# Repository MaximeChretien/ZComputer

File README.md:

# ZComputer

This projects aims to build a computer based on a Z80 CPU from scratch.

## Introduction

The computer is designed as a set of boards, each having a specific function.

The current planned boards are:
- Main (CPU, RAM, ROM, ...)
- Basic I/O
- Interrupt (Interrupt vector decoding and prioritizing)
- UART
- Counter/Timer
- ADC and DAC
- Storage

Those boards will then connect on the base board through a unified connector.  
The base board also includes the power input and the reset button as well as a power LED.

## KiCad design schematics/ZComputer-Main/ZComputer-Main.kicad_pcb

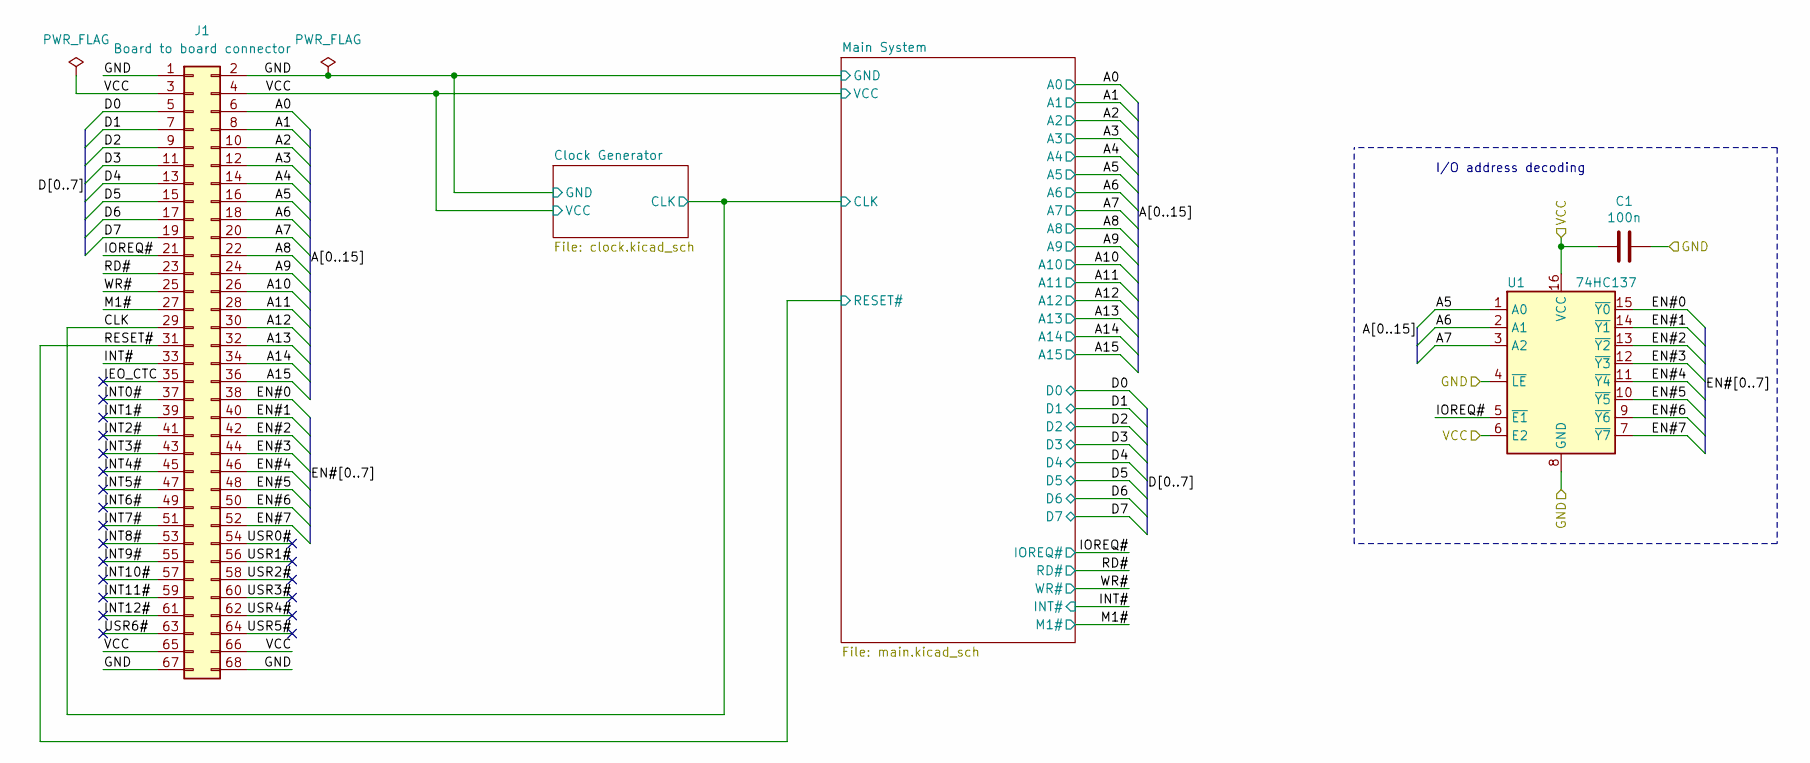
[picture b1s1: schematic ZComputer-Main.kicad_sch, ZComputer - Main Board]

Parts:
C1: 100n; C_Disc_D4.3mm_W1.9mm_P5.00mm
J1: Board to board connector; PinSocket_2x34_P2.54mm_Horizontal
U1: 74HC137; DIP-16_W7.62mm_Socket_LongPads

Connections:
/A0: J1.6; also elsewhere on the board
/A1: J1.8; also elsewhere on the board
/A2: J1.10; also elsewhere on the board
/A3: J1.12; also elsewhere on the board
/A4: J1.14; also elsewhere on the board
/A5: J1.16, U1.1 (A0); also elsewhere on the board
/A6: J1.18, U1.2 (A1); also elsewhere on the board
/A7: J1.20, U1.3 (A2); also elsewhere on the board
/A8: J1.22; also elsewhere on the board
/A9: J1.24; also elsewhere on the board
/A10: J1.26; also elsewhere on the board
/A11: J1.28; also elsewhere on the board
/A12: J1.30; also elsewhere on the board
/A13: J1.32; also elsewhere on the board
/A14: J1.34; also elsewhere on the board
/A15: J1.36; also elsewhere on the board
/CLK: J1.29; also elsewhere on the board
/D0: J1.5; also elsewhere on the board
/D1: J1.7; also elsewhere on the board
/D2: J1.9; also elsewhere on the board
/D3: J1.11; also elsewhere on the board
/D4: J1.13; also elsewhere on the board
/D5: J1.15; also elsewhere on the board
/D6: J1.17; also elsewhere on the board
/D7: J1.19; also elsewhere on the board
/EN#0: J1.38, U1.15 (~Y0)
/EN#1: J1.40, U1.14 (~Y1)
/EN#2: J1.42, U1.13 (~Y2)
/EN#3: J1.44, U1.12 (~Y3)
/EN#4: J1.46, U1.11 (~Y4)
/EN#5: J1.48, U1.10 (~Y5)
/EN#6: J1.50, U1.9 (~Y6)
/EN#7: J1.52, U1.7 (~Y7)
/GND: C1.1, J1.1, J1.2, J1.67, J1.68, U1.4 (~LE), U1.8 (GND); also elsewhere on the board
/IEO_CTC: J1.35
/INT0#: J1.37
/INT1#: J1.39
/INT2#: J1.41
/INT3#: J1.43
/INT4#: J1.45
/INT5#: J1.47
/INT6#: J1.49
/INT7#: J1.51
/INT8#: J1.53
/INT9#: J1.55
/INT10#: J1.57
/INT11#: J1.59
/INT12#: J1.61
/INT#: J1.33; also elsewhere on the board
/IOREQ#: J1.21, U1.5 (~E1); also elsewhere on the board
/M1#: J1.27; also elsewhere on the board
/RD#: J1.23; also elsewhere on the board
/RESET#: J1.31; also elsewhere on the board
/USR0#: J1.54
/USR1#: J1.56
/USR2#: J1.58
/USR3#: J1.60
/USR4#: J1.62
/USR5#: J1.64
/USR6#: J1.63
/VCC: C1.2, J1.3, J1.4, J1.65, J1.66, U1.6 (E2), U1.16 (VCC); also elsewhere on the board
/WR#: J1.25; also elsewhere on the board

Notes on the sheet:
I/O address decoding

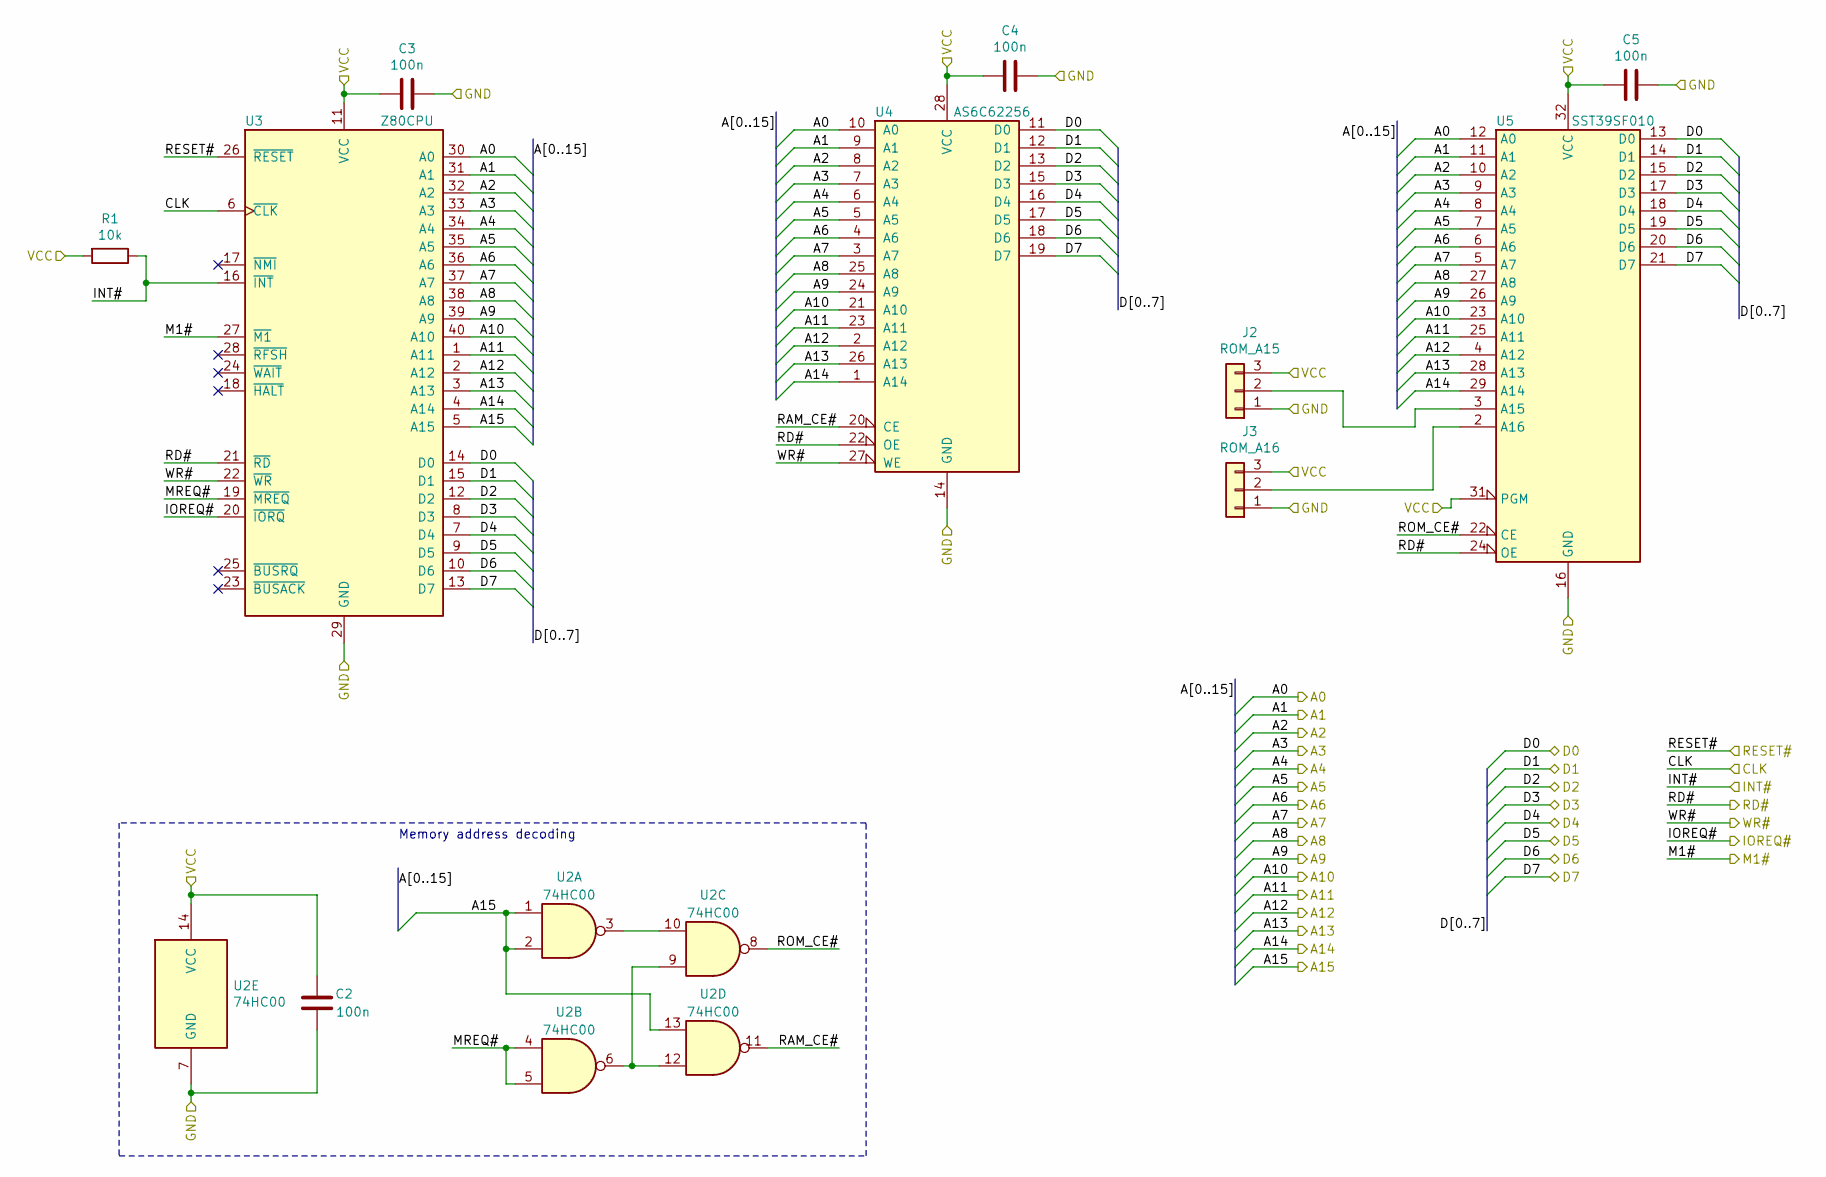
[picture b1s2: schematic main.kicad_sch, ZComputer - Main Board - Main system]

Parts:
C2, C3, C4, C5: 100n; C_Disc_D4.3mm_W1.9mm_P5.00mm
J2: ROM_A15; PinHeader_1x03_P2.54mm_Vertical
J3: ROM_A16; PinHeader_1x03_P2.54mm_Vertical
R1: 10k; R_Axial_DIN0207_L6.3mm_D2.5mm_P10.16mm_Horizontal
U2: 74HC00; DIP-14_W7.62mm_Socket_LongPads
U3: Z80CPU; DIP-40_W15.24mm_Socket_LongPads
U4: AS6C62256; DIP-28_W15.24mm_Socket_LongPads
U5: SST39SF010; DIP-32_W15.24mm_Socket_LongPads

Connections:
/A0: U3.30 (A0), U4.10 (A0), U5.12 (A0); also elsewhere on the board
/A1: U3.31 (A1), U4.9 (A1), U5.11 (A1); also elsewhere on the board
/A2: U3.32 (A2), U4.8 (A2), U5.10 (A2); also elsewhere on the board
/A3: U3.33 (A3), U4.7 (A3), U5.9 (A3); also elsewhere on the board
/A4: U3.34 (A4), U4.6 (A4), U5.8 (A4); also elsewhere on the board
/A5: U3.35 (A5), U4.5 (A5), U5.7 (A5); also elsewhere on the board
/A6: U3.36 (A6), U4.4 (A6), U5.6 (A6); also elsewhere on the board
/A7: U3.37 (A7), U4.3 (A7), U5.5 (A7); also elsewhere on the board
/A8: U3.38 (A8), U4.25 (A8), U5.27 (A8); also elsewhere on the board
/A9: U3.39 (A9), U4.24 (A9), U5.26 (A9); also elsewhere on the board
/A10: U3.40 (A10), U4.21 (A10), U5.23 (A10); also elsewhere on the board
/A11: U3.1 (A11), U4.23 (A11), U5.25 (A11); also elsewhere on the board
/A12: U3.2 (A12), U4.2 (A12), U5.4 (A12); also elsewhere on the board
/A13: U3.3 (A13), U4.26 (A13), U5.28 (A13); also elsewhere on the board
/A14: U3.4 (A14), U4.1 (A14), U5.29 (A14); also elsewhere on the board
/A15: U2.1, U2.2, U2.13, U3.5 (A15); also elsewhere on the board
/CLK: U3.6 (~CLK); also elsewhere on the board
/D0: U3.14 (D0), U4.11 (D0), U5.13 (D0); also elsewhere on the board
/D1: U3.15 (D1), U4.12 (D1), U5.14 (D1); also elsewhere on the board
/D2: U3.12 (D2), U4.13 (D2), U5.15 (D2); also elsewhere on the board
/D3: U3.8 (D3), U4.15 (D3), U5.17 (D3); also elsewhere on the board
/D4: U3.7 (D4), U4.16 (D4), U5.18 (D4); also elsewhere on the board
/D5: U3.9 (D5), U4.17 (D5), U5.19 (D5); also elsewhere on the board
/D6: U3.10 (D6), U4.18 (D6), U5.20 (D6); also elsewhere on the board
/D7: U3.13 (D7), U4.19 (D7), U5.21 (D7); also elsewhere on the board
/GND: C2.1, C3.1, C4.1, C5.1, J2.1, J3.1, U2.7 (GND), U3.29 (GND), U4.14 (GND), U5.16 (GND); also elsewhere on the board
/INT#: R1.1, U3.16 (~INT); also elsewhere on the board
/IOREQ#: U3.20 (~IORQ); also elsewhere on the board
/M1#: U3.27 (~M1); also elsewhere on the board
/Main System/MREQ#: U2.4, U2.5, U3.19 (~MREQ)
/Main System/RAM_CE#: U2.11, U4.20 (CE)
/Main System/ROM_CE#: U2.8, U5.22 (CE)
/RD#: U3.21 (~RD), U4.22 (OE), U5.24 (OE); also elsewhere on the board
/RESET#: U3.26 (~RESET); also elsewhere on the board
/VCC: C2.2, C3.2, C4.2, C5.2, J2.3, J3.3, R1.2, U2.14 (VCC), U3.11 (VCC), U4.28 (VCC), U5.31 (PGM), U5.32 (VCC); also elsewhere on the board
/WR#: U3.22 (~WR), U4.27 (WE); also elsewhere on the board
unnamed: J2.2, U5.3 (A15)
unnamed: J3.2, U5.2 (A16)
unnamed: U2.3, U2.10
unnamed: U2.6, U2.9, U2.12

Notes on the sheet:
Memory address decoding

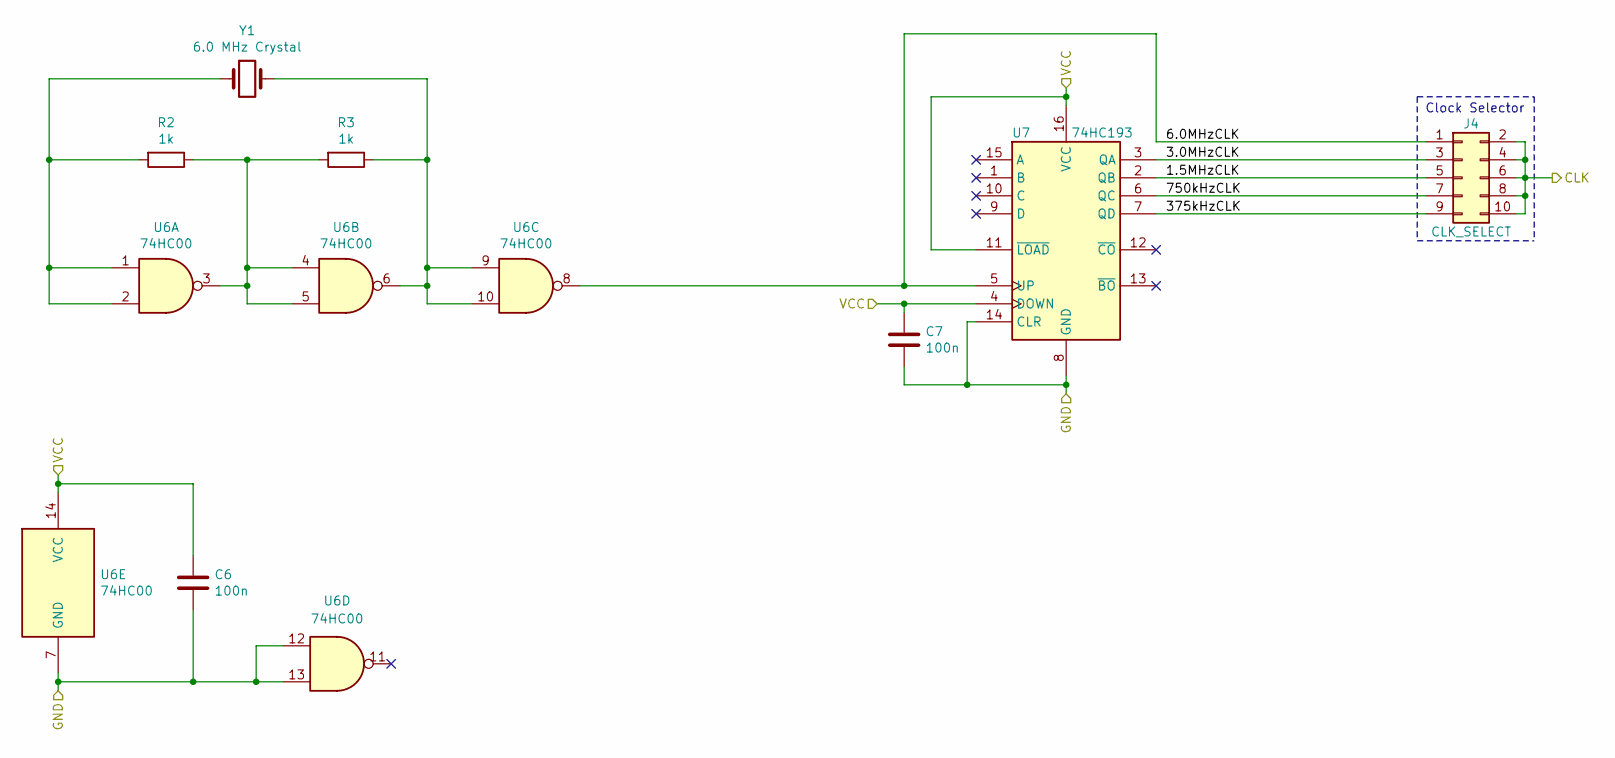
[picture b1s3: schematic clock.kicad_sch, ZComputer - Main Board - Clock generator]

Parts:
C6, C7: 100n; C_Disc_D4.3mm_W1.9mm_P5.00mm
J4: CLK_SELECT; PinHeader_2x05_P2.54mm_Vertical
R2, R3: 1k; R_Axial_DIN0207_L6.3mm_D2.5mm_P10.16mm_Horizontal
U6: 74HC00; DIP-14_W7.62mm_Socket_LongPads
U7: 74HC193; DIP-16_W7.62mm_Socket_LongPads
Y1: 6.0 MHz Crystal; Crystal_HC49-4H_Vertical

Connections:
/CLK: J4.2, J4.4, J4.6, J4.8, J4.10; also elsewhere on the board
/Clock Generator/1.5MHzCLK: J4.5, U7.2 (QB)
/Clock Generator/3.0MHzCLK: J4.3, U7.3 (QA)
/Clock Generator/6.0MHzCLK: J4.1, U6.8, U7.5 (UP)
/Clock Generator/375kHzCLK: J4.9, U7.7 (QD)
/Clock Generator/750kHzCLK: J4.7, U7.6 (QC)
/GND: C6.2, C7.2, U6.7 (GND), U6.12, U6.13, U7.8 (GND), U7.14 (CLR); also elsewhere on the board
/VCC: C6.1, C7.1, U6.14 (VCC), U7.4 (DOWN), U7.11 (~LOAD), U7.16 (VCC); also elsewhere on the board
unnamed: R2.1, R3.2, U6.3, U6.4, U6.5
unnamed: R2.2, U6.1, U6.2, Y1.1
unnamed: R3.1, U6.6, U6.9, U6.10, Y1.2

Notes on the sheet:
Clock Selector

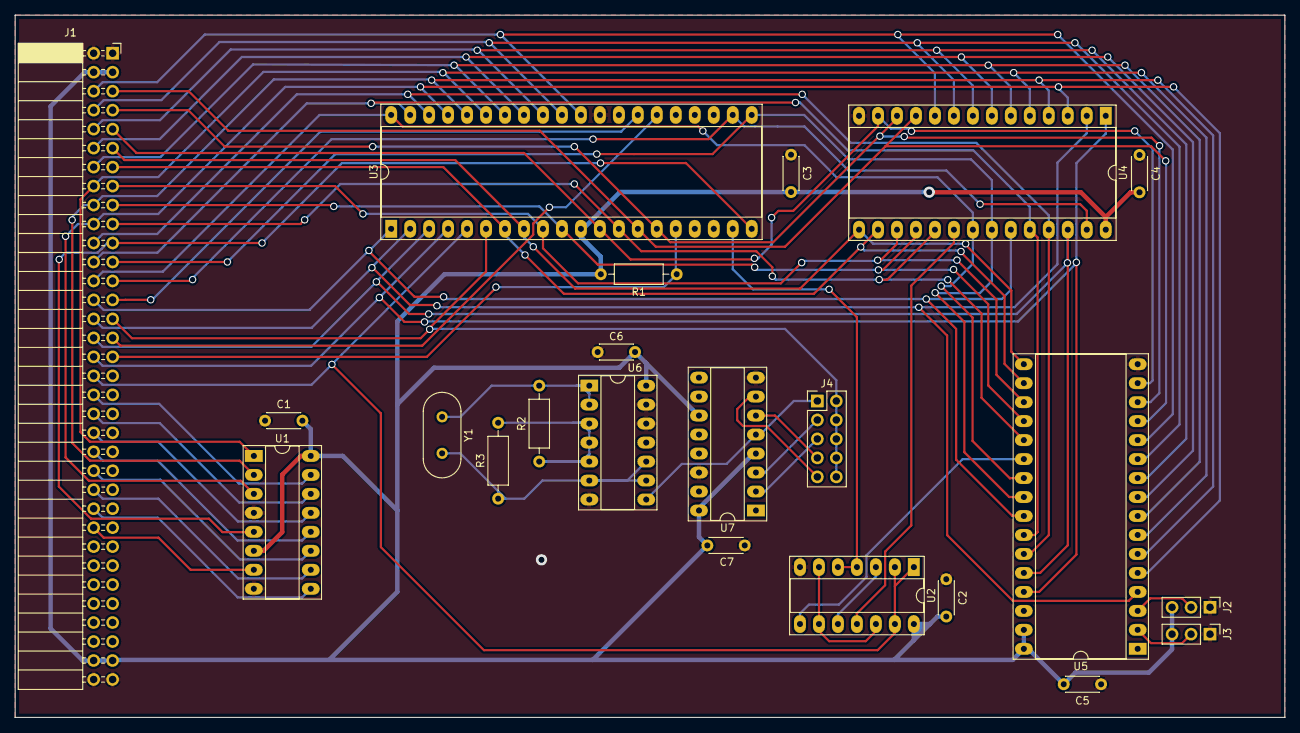
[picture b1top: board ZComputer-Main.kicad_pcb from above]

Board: 2 copper layers, 169.9 x 94.0 mm, 22 parts (0 on the bottom side), 56 nets.

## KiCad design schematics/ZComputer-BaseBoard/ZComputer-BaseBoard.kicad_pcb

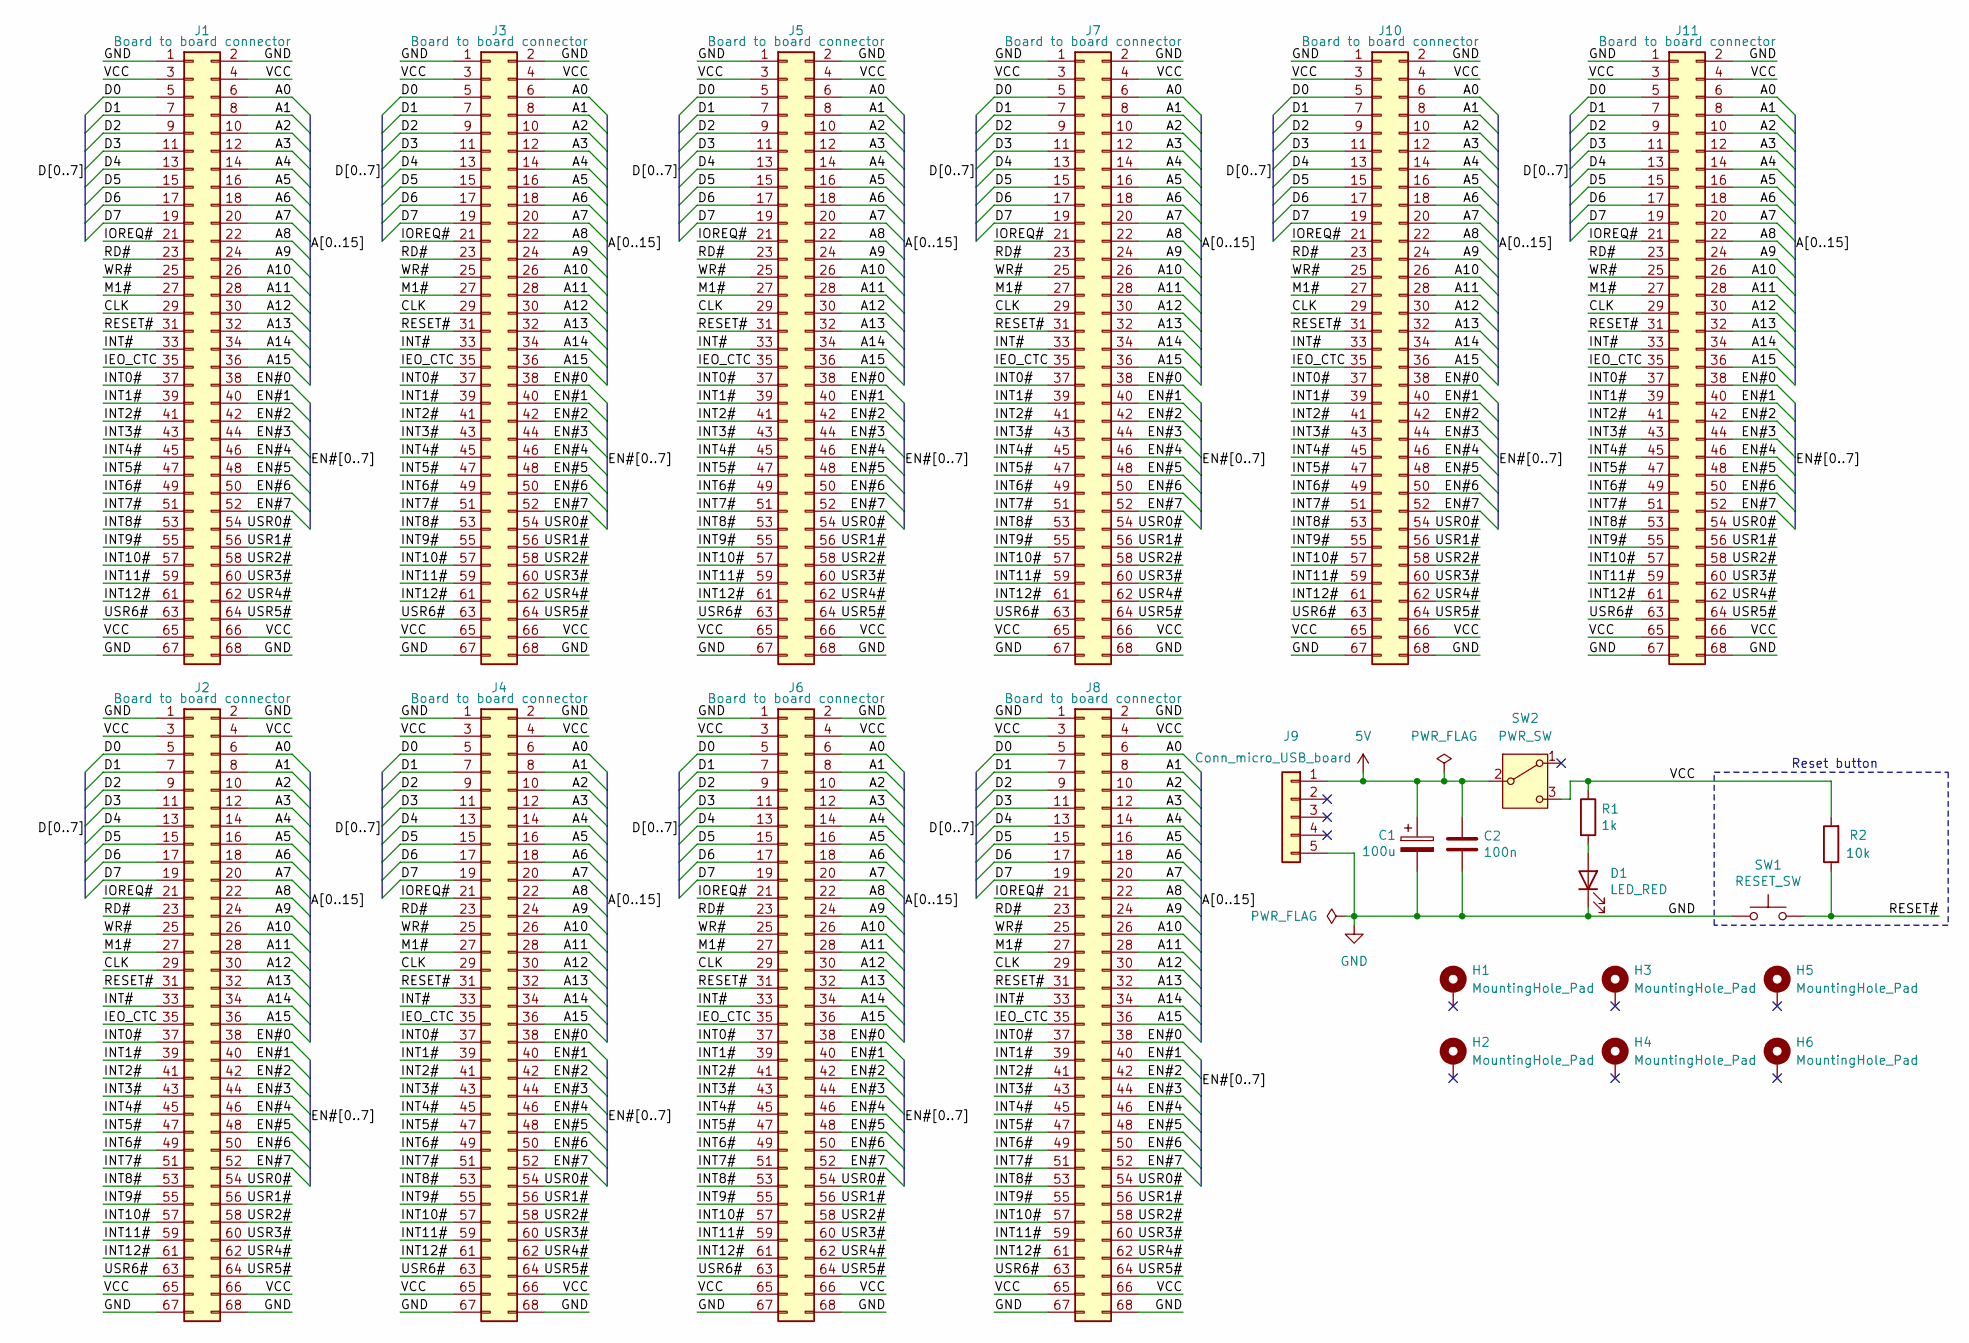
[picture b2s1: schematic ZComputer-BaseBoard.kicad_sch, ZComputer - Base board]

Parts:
C1: 100u; CP_Radial_D8.0mm_P2.50mm
C2: 100n; C_Disc_D4.3mm_W1.9mm_P5.00mm
D1: LED_RED; LED_D5.0mm
H1, H2, H3, H4, H5, H6: MountingHole_Pad; MountingHole_2.7mm_Pad
J1, J2, J3, J4, J5, J6, J7, J8, J10, J11: Board to board connector; PinHeader_2x34_P2.54mm_Vertical
J9: Conn_micro_USB_board; PinHeader_1x05_P2.54mm_Vertical
R1: 1k; R_Axial_DIN0207_L6.3mm_D2.5mm_P10.16mm_Horizontal
R2: 10k; R_Axial_DIN0207_L6.3mm_D2.5mm_P10.16mm_Horizontal
SW1: RESET_SW; SW_PUSH_6mm_H4.3mm
SW2: PWR_SW; SW_Slide_SPDT_Angled_CK_OS102011MA1Q

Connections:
5V: C1.1, C2.1, J9.1, SW2.2 (B)
/A0: J1.6, J2.6, J3.6, J4.6, J5.6, J6.6, J7.6, J8.6, J10.6, J11.6
/A1: J1.8, J2.8, J3.8, J4.8, J5.8, J6.8, J7.8, J8.8, J10.8, J11.8
/A2: J1.10, J2.10, J3.10, J4.10, J5.10, J6.10, J7.10, J8.10, J10.10, J11.10
/A3: J1.12, J2.12, J3.12, J4.12, J5.12, J6.12, J7.12, J8.12, J10.12, J11.12
/A4: J1.14, J2.14, J3.14, J4.14, J5.14, J6.14, J7.14, J8.14, J10.14, J11.14
/A5: J1.16, J2.16, J3.16, J4.16, J5.16, J6.16, J7.16, J8.16, J10.16, J11.16
/A6: J1.18, J2.18, J3.18, J4.18, J5.18, J6.18, J7.18, J8.18, J10.18, J11.18
/A7: J1.20, J2.20, J3.20, J4.20, J5.20, J6.20, J7.20, J8.20, J10.20, J11.20
/A8: J1.22, J2.22, J3.22, J4.22, J5.22, J6.22, J7.22, J8.22, J10.22, J11.22
/A9: J1.24, J2.24, J3.24, J4.24, J5.24, J6.24, J7.24, J8.24, J10.24, J11.24
/A10: J1.26, J2.26, J3.26, J4.26, J5.26, J6.26, J7.26, J8.26, J10.26, J11.26
/A11: J1.28, J2.28, J3.28, J4.28, J5.28, J6.28, J7.28, J8.28, J10.28, J11.28
/A12: J1.30, J2.30, J3.30, J4.30, J5.30, J6.30, J7.30, J8.30, J10.30, J11.30
/A13: J1.32, J2.32, J3.32, J4.32, J5.32, J6.32, J7.32, J8.32, J10.32, J11.32
/A14: J1.34, J2.34, J3.34, J4.34, J5.34, J6.34, J7.34, J8.34, J10.34, J11.34
/A15: J1.36, J2.36, J3.36, J4.36, J5.36, J6.36, J7.36, J8.36, J10.36, J11.36
/CLK: J1.29, J2.29, J3.29, J4.29, J5.29, J6.29, J7.29, J8.29, J10.29, J11.29
/D0: J1.5, J2.5, J3.5, J4.5, J5.5, J6.5, J7.5, J8.5, J10.5, J11.5
/D1: J1.7, J2.7, J3.7, J4.7, J5.7, J6.7, J7.7, J8.7, J10.7, J11.7
/D2: J1.9, J2.9, J3.9, J4.9, J5.9, J6.9, J7.9, J8.9, J10.9, J11.9
/D3: J1.11, J2.11, J3.11, J4.11, J5.11, J6.11, J7.11, J8.11, J10.11, J11.11
/D4: J1.13, J2.13, J3.13, J4.13, J5.13, J6.13, J7.13, J8.13, J10.13, J11.13
/D5: J1.15, J2.15, J3.15, J4.15, J5.15, J6.15, J7.15, J8.15, J10.15, J11.15
/D6: J1.17, J2.17, J3.17, J4.17, J5.17, J6.17, J7.17, J8.17, J10.17, J11.17
/D7: J1.19, J2.19, J3.19, J4.19, J5.19, J6.19, J7.19, J8.19, J10.19, J11.19
/EN#0: J1.38, J2.38, J3.38, J4.38, J5.38, J6.38, J7.38, J8.38, J10.38, J11.38
/EN#1: J1.40, J2.40, J3.40, J4.40, J5.40, J6.40, J7.40, J8.40, J10.40, J11.40
/EN#2: J1.42, J2.42, J3.42, J4.42, J5.42, J6.42, J7.42, J8.42, J10.42, J11.42
/EN#3: J1.44, J2.44, J3.44, J4.44, J5.44, J6.44, J7.44, J8.44, J10.44, J11.44
/EN#4: J1.46, J2.46, J3.46, J4.46, J5.46, J6.46, J7.46, J8.46, J10.46, J11.46
/EN#5: J1.48, J2.48, J3.48, J4.48, J5.48, J6.48, J7.48, J8.48, J10.48, J11.48
/EN#6: J1.50, J2.50, J3.50, J4.50, J5.50, J6.50, J7.50, J8.50, J10.50, J11.50
/EN#7: J1.52, J2.52, J3.52, J4.52, J5.52, J6.52, J7.52, J8.52, J10.52, J11.52
/IEO_CTC: J1.35, J2.35, J3.35, J4.35, J5.35, J6.35, J7.35, J8.35, J10.35, J11.35
/INT0#: J1.37, J2.37, J3.37, J4.37, J5.37, J6.37, J7.37, J8.37, J10.37, J11.37
/INT1#: J1.39, J2.39, J3.39, J4.39, J5.39, J6.39, J7.39, J8.39, J10.39, J11.39
/INT2#: J1.41, J2.41, J3.41, J4.41, J5.41, J6.41, J7.41, J8.41, J10.41, J11.41
/INT3#: J1.43, J2.43, J3.43, J4.43, J5.43, J6.43, J7.43, J8.43, J10.43, J11.43
/INT4#: J1.45, J2.45, J3.45, J4.45, J5.45, J6.45, J7.45, J8.45, J10.45, J11.45
/INT5#: J1.47, J2.47, J3.47, J4.47, J5.47, J6.47, J7.47, J8.47, J10.47, J11.47
/INT6#: J1.49, J2.49, J3.49, J4.49, J5.49, J6.49, J7.49, J8.49, J10.49, J11.49
/INT7#: J1.51, J2.51, J3.51, J4.51, J5.51, J6.51, J7.51, J8.51, J10.51, J11.51
/INT8#: J1.53, J2.53, J3.53, J4.53, J5.53, J6.53, J7.53, J8.53, J10.53, J11.53
/INT9#: J1.55, J2.55, J3.55, J4.55, J5.55, J6.55, J7.55, J8.55, J10.55, J11.55
/INT10#: J1.57, J2.57, J3.57, J4.57, J5.57, J6.57, J7.57, J8.57, J10.57, J11.57
/INT11#: J1.59, J2.59, J3.59, J4.59, J5.59, J6.59, J7.59, J8.59, J10.59, J11.59
/INT12#: J1.61, J2.61, J3.61, J4.61, J5.61, J6.61, J7.61, J8.61, J10.61, J11.61
/INT#: J1.33, J2.33, J3.33, J4.33, J5.33, J6.33, J7.33, J8.33, J10.33, J11.33
/IOREQ#: J1.21, J2.21, J3.21, J4.21, J5.21, J6.21, J7.21, J8.21, J10.21, J11.21
/M1#: J1.27, J2.27, J3.27, J4.27, J5.27, J6.27, J7.27, J8.27, J10.27, J11.27
/RD#: J1.23, J2.23, J3.23, J4.23, J5.23, J6.23, J7.23, J8.23, J10.23, J11.23
/RESET#: J1.31, J2.31, J3.31, J4.31, J5.31, J6.31, J7.31, J8.31, J10.31, J11.31, R2.1, SW1.2
/USR0#: J1.54, J2.54, J3.54, J4.54, J5.54, J6.54, J7.54, J8.54, J10.54, J11.54
/USR1#: J1.56, J2.56, J3.56, J4.56, J5.56, J6.56, J7.56, J8.56, J10.56, J11.56
/USR2#: J1.58, J2.58, J3.58, J4.58, J5.58, J6.58, J7.58, J8.58, J10.58, J11.58
/USR3#: J1.60, J2.60, J3.60, J4.60, J5.60, J6.60, J7.60, J8.60, J10.60, J11.60
/USR4#: J1.62, J2.62, J3.62, J4.62, J5.62, J6.62, J7.62, J8.62, J10.62, J11.62
/USR5#: J1.64, J2.64, J3.64, J4.64, J5.64, J6.64, J7.64, J8.64, J10.64, J11.64
/USR6#: J1.63, J2.63, J3.63, J4.63, J5.63, J6.63, J7.63, J8.63, J10.63, J11.63
/VCC: J1.3, J1.4, J1.65, J1.66, J2.3, J2.4, J2.65, J2.66, J3.3, J3.4, J3.65, J3.66, J4.3, J4.4, J4.65, J4.66, J5.3, J5.4, J5.65, J5.66, J6.3, J6.4, J6.65, J6.66, J7.3, J7.4, J7.65, J7.66, J8.3, J8.4, J8.65, J8.66, J10.3, J10.4, J10.65, J10.66, J11.3, J11.4, J11.65, J11.66, R1.1, R2.2, SW2.3 (C)
/WR#: J1.25, J2.25, J3.25, J4.25, J5.25, J6.25, J7.25, J8.25, J10.25, J11.25
GND: C1.2, C2.2, D1.1 (K), J1.1, J1.2, J1.67, J1.68, J2.1, J2.2, J2.67, J2.68, J3.1, J3.2, J3.67, J3.68, J4.1, J4.2, J4.67, J4.68, J5.1, J5.2, J5.67, J5.68, J6.1, J6.2, J6.67, J6.68, J7.1, J7.2, J7.67, J7.68, J8.1, J8.2, J8.67, J8.68, J9.5, J10.1, J10.2, J10.67, J10.68, J11.1, J11.2, J11.67, J11.68, SW1.1
unnamed: D1.2 (A), R1.2

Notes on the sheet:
Reset button

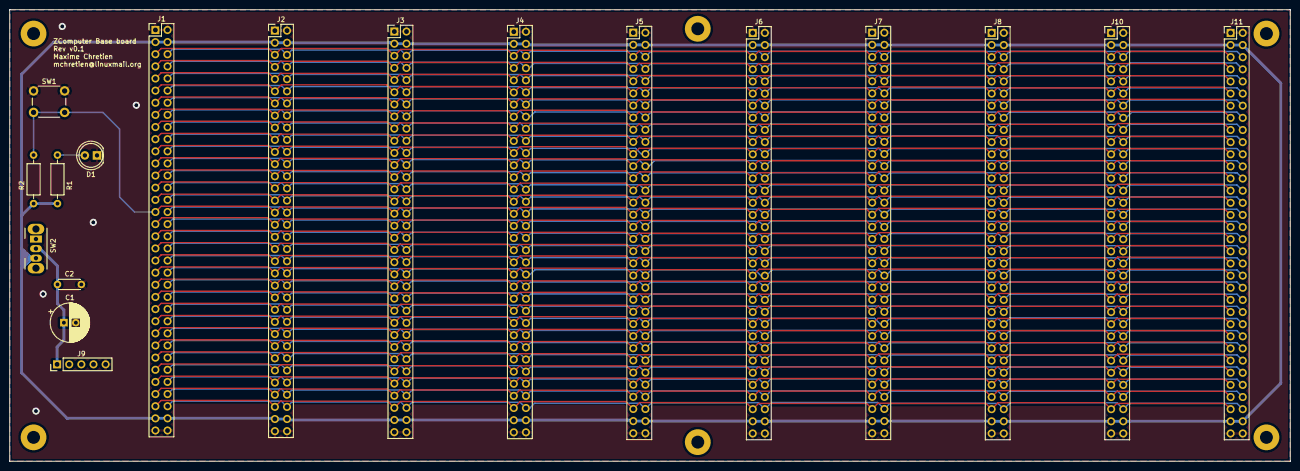
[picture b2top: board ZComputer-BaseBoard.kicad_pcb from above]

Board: 2 copper layers, 268.0 x 94.5 mm, 24 parts (0 on the bottom side), 64 nets.

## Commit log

2022-10-11 Migrate to KiCad 6
2024-06-10 Move old schematics to a new folder
2024-06-10 Add new Main board schematics
    This is done with KiCAD 8.0 now.
2024-06-11 Add base board schematic and PCB design
2024-06-11 Add more information to ReadMe.md
2024-06-13 Remove old files
2024-06-13 Add power switch on the base board
2024-06-21 Add 74HC32 to shared lib
2024-06-21 Add I/O ports board schematics
2024-07-05 Main board: Add PCB layout
